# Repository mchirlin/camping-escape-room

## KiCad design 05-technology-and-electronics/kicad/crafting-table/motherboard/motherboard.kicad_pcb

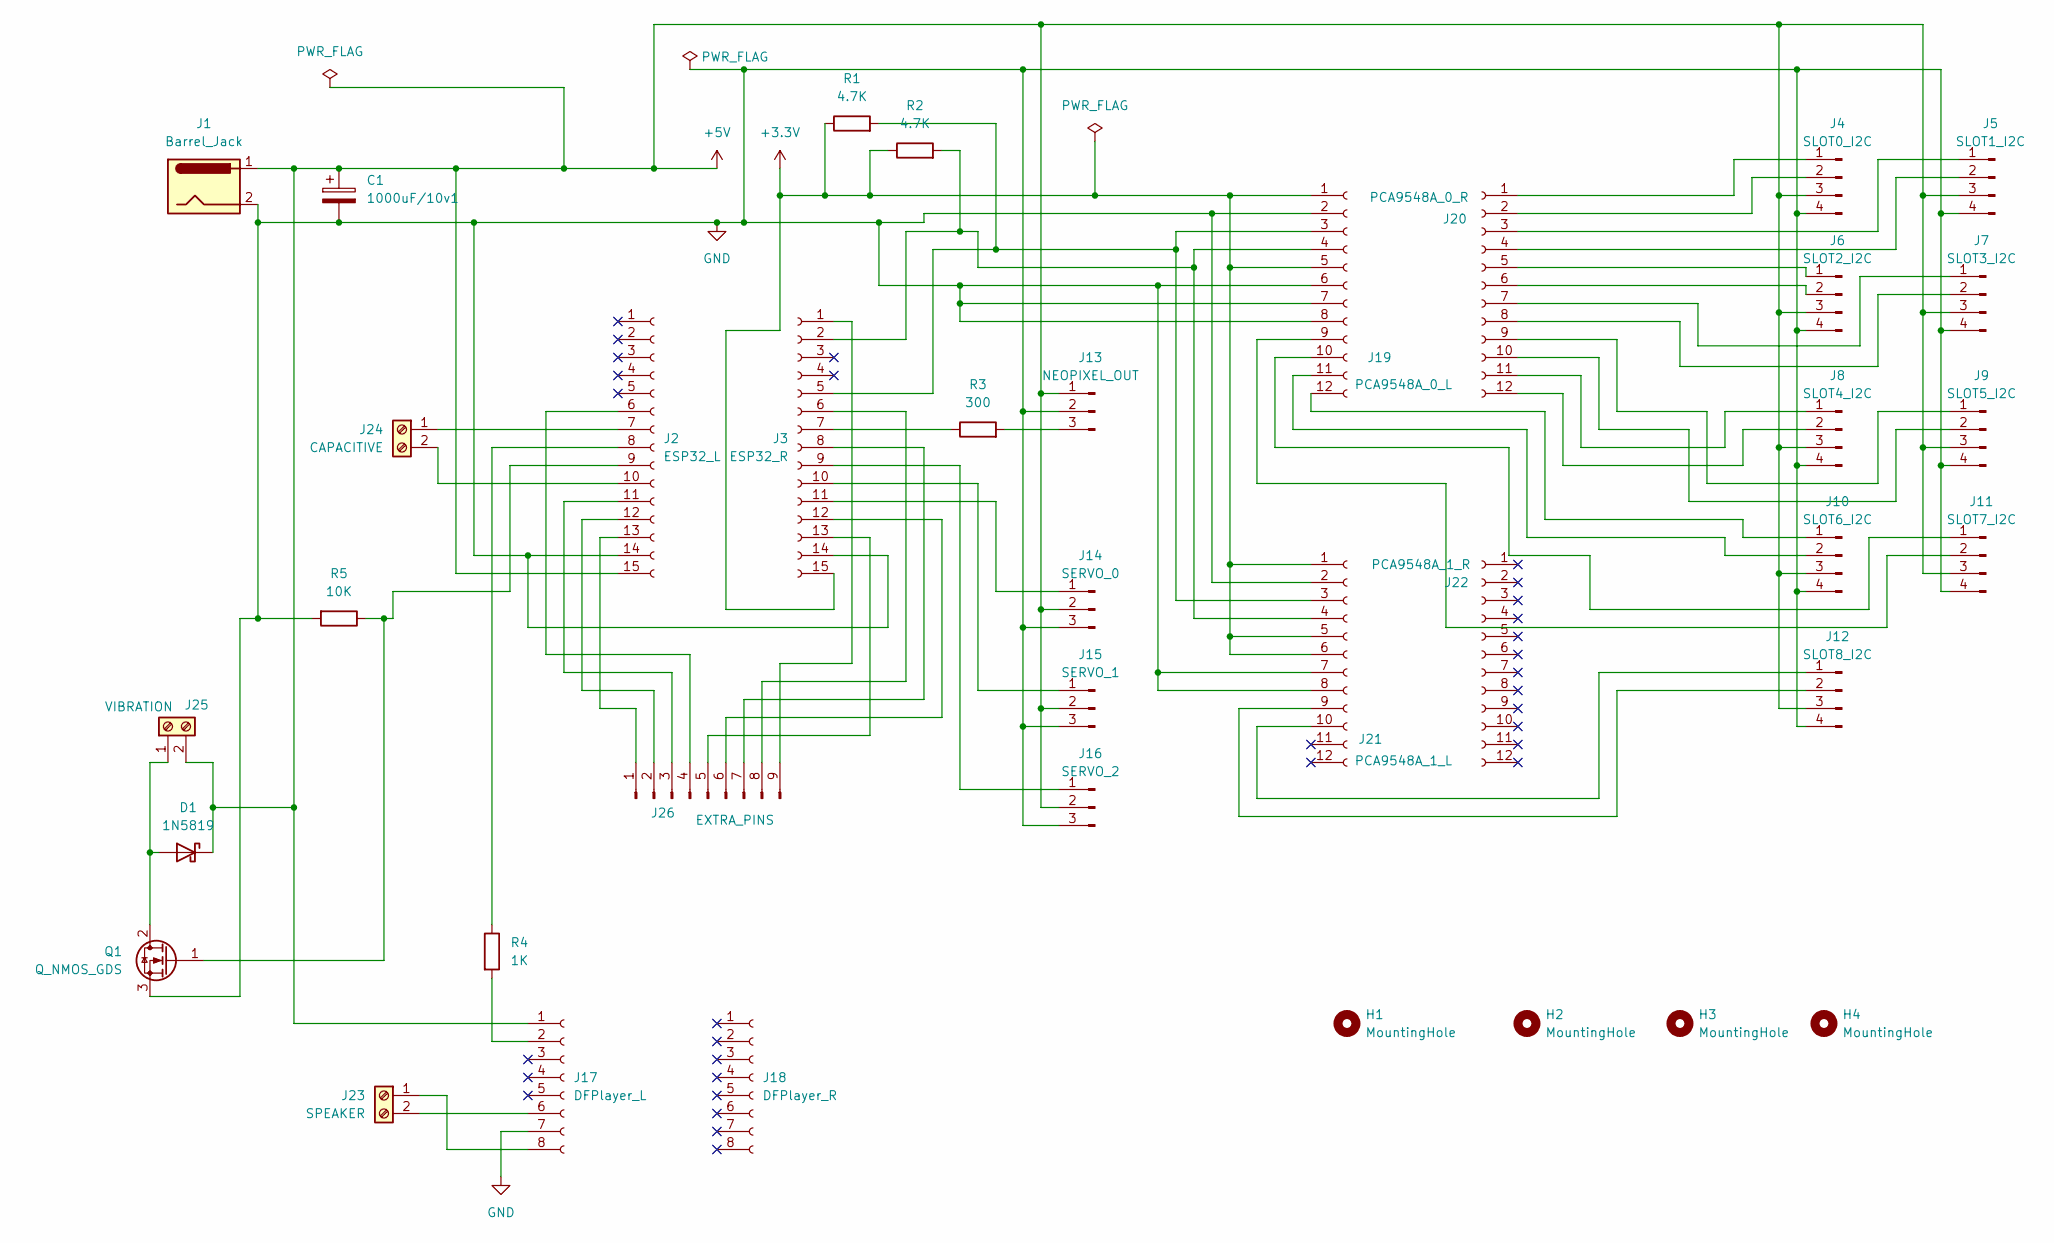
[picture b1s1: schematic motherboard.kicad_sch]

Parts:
C1: 1000uF/10v1; CP_Radial_D10.0mm_P5.00mm
D1: 1N5819; D_DO-41_SOD81_P10.16mm_Horizontal
H1, H2, H3, H4: MountingHole; MountingHole_3.2mm_M3
J1: Barrel_Jack; BarrelJack_Horizontal
J2: ESP32_L; PinSocket_1x15_P2.54mm_Vertical
J3: ESP32_R; PinSocket_1x15_P2.54mm_Vertical
J4: SLOT0_I2C; JST_XH_B4B-XH-A_1x04_P2.50mm_Vertical
J5: SLOT1_I2C; JST_XH_B4B-XH-A_1x04_P2.50mm_Vertical
J6: SLOT2_I2C; JST_XH_B4B-XH-A_1x04_P2.50mm_Vertical
J7: SLOT3_I2C; JST_XH_B4B-XH-A_1x04_P2.50mm_Vertical
J8: SLOT4_I2C; JST_XH_B4B-XH-A_1x04_P2.50mm_Vertical
J9: SLOT5_I2C; JST_XH_B4B-XH-A_1x04_P2.50mm_Vertical
J10: SLOT6_I2C; JST_XH_B4B-XH-A_1x04_P2.50mm_Vertical
J11: SLOT7_I2C; JST_XH_B4B-XH-A_1x04_P2.50mm_Vertical
J12: SLOT8_I2C; JST_XH_B4B-XH-A_1x04_P2.50mm_Vertical
J13: NEOPIXEL_OUT; JST_XH_B3B-XH-A_1x03_P2.50mm_Vertical
J14: SERVO_0; JST_XH_B3B-XH-A_1x03_P2.50mm_Vertical
J15: SERVO_1; JST_XH_B3B-XH-A_1x03_P2.50mm_Vertical
J16: SERVO_2; JST_XH_B3B-XH-A_1x03_P2.50mm_Vertical
J17: DFPlayer_L; PinSocket_1x08_P2.54mm_Vertical
J18: DFPlayer_R; PinSocket_1x08_P2.54mm_Vertical
J19: PCA9548A_0_L; PinSocket_1x12_P2.54mm_Vertical
J20: PCA9548A_0_R; PinSocket_1x12_P2.54mm_Vertical
J21: PCA9548A_1_L; PinSocket_1x12_P2.54mm_Vertical
J22: PCA9548A_1_R; PinSocket_1x12_P2.54mm_Vertical
J23: SPEAKER; TerminalBlock_TE_282834-2_1x02_P2.54mm_Horizontal
J24: CAPACITIVE; TerminalBlock_TE_282834-2_1x02_P2.54mm_Horizontal
J25: VIBRATION; TerminalBlock_TE_282834-2_1x02_P2.54mm_Horizontal
J26: EXTRA_PINS; PinHeader_1x09_P2.54mm_Vertical
Q1: Q_NMOS_GDS; TO-220-3_Vertical
R1, R2: 4.7K; R_Axial_DIN0207_L6.3mm_D2.5mm_P10.16mm_Horizontal
R3: 300; R_Axial_DIN0207_L6.3mm_D2.5mm_P10.16mm_Horizontal
R4: 1K; R_Axial_DIN0207_L6.3mm_D2.5mm_P10.16mm_Horizontal
R5: 10K; R_Axial_DIN0207_L6.3mm_D2.5mm_P10.16mm_Horizontal

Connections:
+3.3V: J3.15, J19.1, J19.5, J21.1, J21.5, J21.6, R1.1, R2.1
+5V: C1.1, D1.1 (K), J1.1, J2.15, J4.3, J5.3, J6.3, J7.3, J8.3, J9.3, J10.3, J11.3, J12.3, J13.1, J14.2, J15.2, J16.2, J17.1, J25.2
GND: C1.2, J1.2, J2.14, J3.14, J4.4, J5.4, J6.4, J7.4, J8.4, J9.4, J10.4, J11.4, J12.4, J13.2, J14.3, J15.3, J16.3, J17.7, J19.2, J19.6, J19.7, J19.8, J21.2, J21.7, J21.8, Q1.3 (S), R5.2
unnamed: D1.2 (A), J25.1, Q1.2 (D)
unnamed: J2.6, J26.4
unnamed: J2.7, J24.1
unnamed: J2.8, R4.1
unnamed: J2.9, Q1.1 (G), R5.1
unnamed: J2.10, J24.2
unnamed: J2.11, J26.3
unnamed: J2.12, J26.2
unnamed: J2.13, J26.1
unnamed: J3.7, R3.1
unnamed: J10.1, J19.12
unnamed: J10.2, J19.11
unnamed: J11.1, J19.10
unnamed: J11.2, J19.9
unnamed: J12.1, J21.10
unnamed: J12.2, J21.9
unnamed: J13.3, R3.2
unnamed: J3.11, J14.1
unnamed: J3.10, J15.1
unnamed: J3.9, J16.1
unnamed: J17.2, R4.2
unnamed: J17.6, J23.2
unnamed: J17.8, J23.1
unnamed: J3.5, J19.3, J21.3, R1.2
unnamed: J3.2, J19.4, J21.4, R2.2
unnamed: J4.1, J20.1
unnamed: J4.2, J20.2
unnamed: J5.1, J20.3
unnamed: J5.2, J20.4
unnamed: J6.1, J20.5
unnamed: J6.2, J20.6
unnamed: J7.1, J20.7
unnamed: J7.2, J20.8
unnamed: J9.1, J20.9
unnamed: J9.2, J20.10
unnamed: J8.1, J20.11
unnamed: J8.2, J20.12
unnamed: J3.13, J26.5
unnamed: J3.12, J26.6
unnamed: J3.8, J26.7
unnamed: J3.6, J26.8
unnamed: J3.1, J26.9

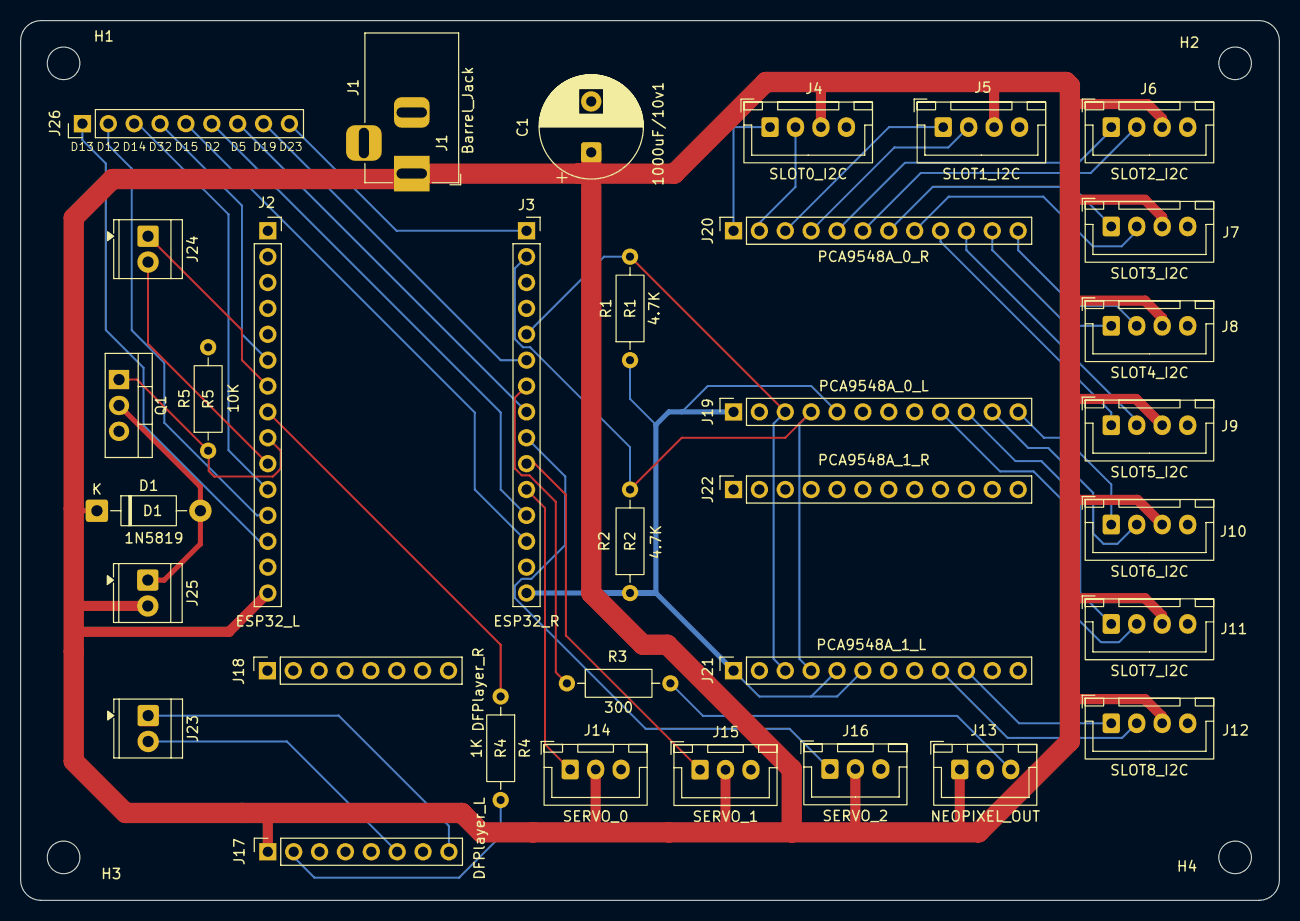
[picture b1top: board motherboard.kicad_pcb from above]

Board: 2 copper layers, 123.6 x 86.4 mm, 38 parts (0 on the bottom side), 45 nets.

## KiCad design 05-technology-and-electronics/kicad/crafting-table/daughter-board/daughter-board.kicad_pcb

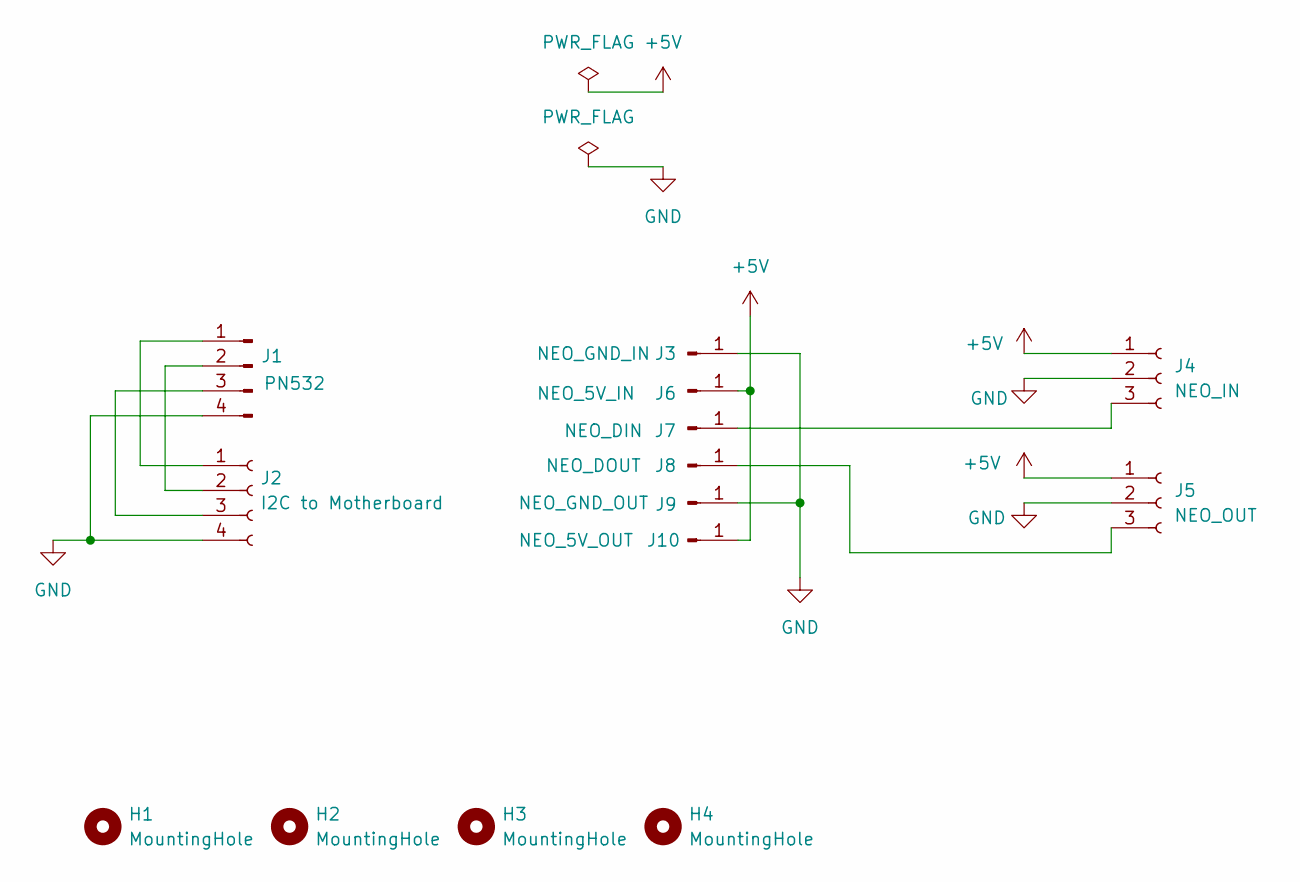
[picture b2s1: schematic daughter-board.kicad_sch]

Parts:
H1, H2, H3, H4: MountingHole; MountingHole_3.2mm_M3
J1: PN532; PinHeader_1x04_P2.54mm_Vertical
J2: I2C to Motherboard; JST_XH_B4B-XH-A_1x04_P2.50mm_Vertical
J3: NEO_GND_IN; PinHeader_1x01_P2.54mm_Vertical
J4: NEO_IN; JST_XH_B3B-XH-A_1x03_P2.50mm_Vertical
J5: NEO_OUT; JST_XH_B3B-XH-A_1x03_P2.50mm_Vertical
J6: NEO_5V_IN; PinHeader_1x01_P2.54mm_Vertical
J7: NEO_DIN; PinHeader_1x01_P2.54mm_Vertical
J8: NEO_DOUT; PinHeader_1x01_P2.54mm_Vertical
J9: NEO_GND_OUT; PinHeader_1x01_P2.54mm_Vertical
J10: NEO_5V_OUT; PinHeader_1x01_P2.54mm_Vertical

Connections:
+5V: J4.1, J5.1, J6.1 (Pin_1_1), J10.1 (Pin_1_1)
GND: J1.4, J2.4, J3.1 (Pin_1_1), J4.2, J5.2, J9.1 (Pin_1_1)
unnamed: J1.1, J2.1
unnamed: J1.2, J2.2
unnamed: J1.3, J2.3
unnamed: J4.3, J7.1 (Pin_1_1)
unnamed: J5.3, J8.1 (Pin_1_1)

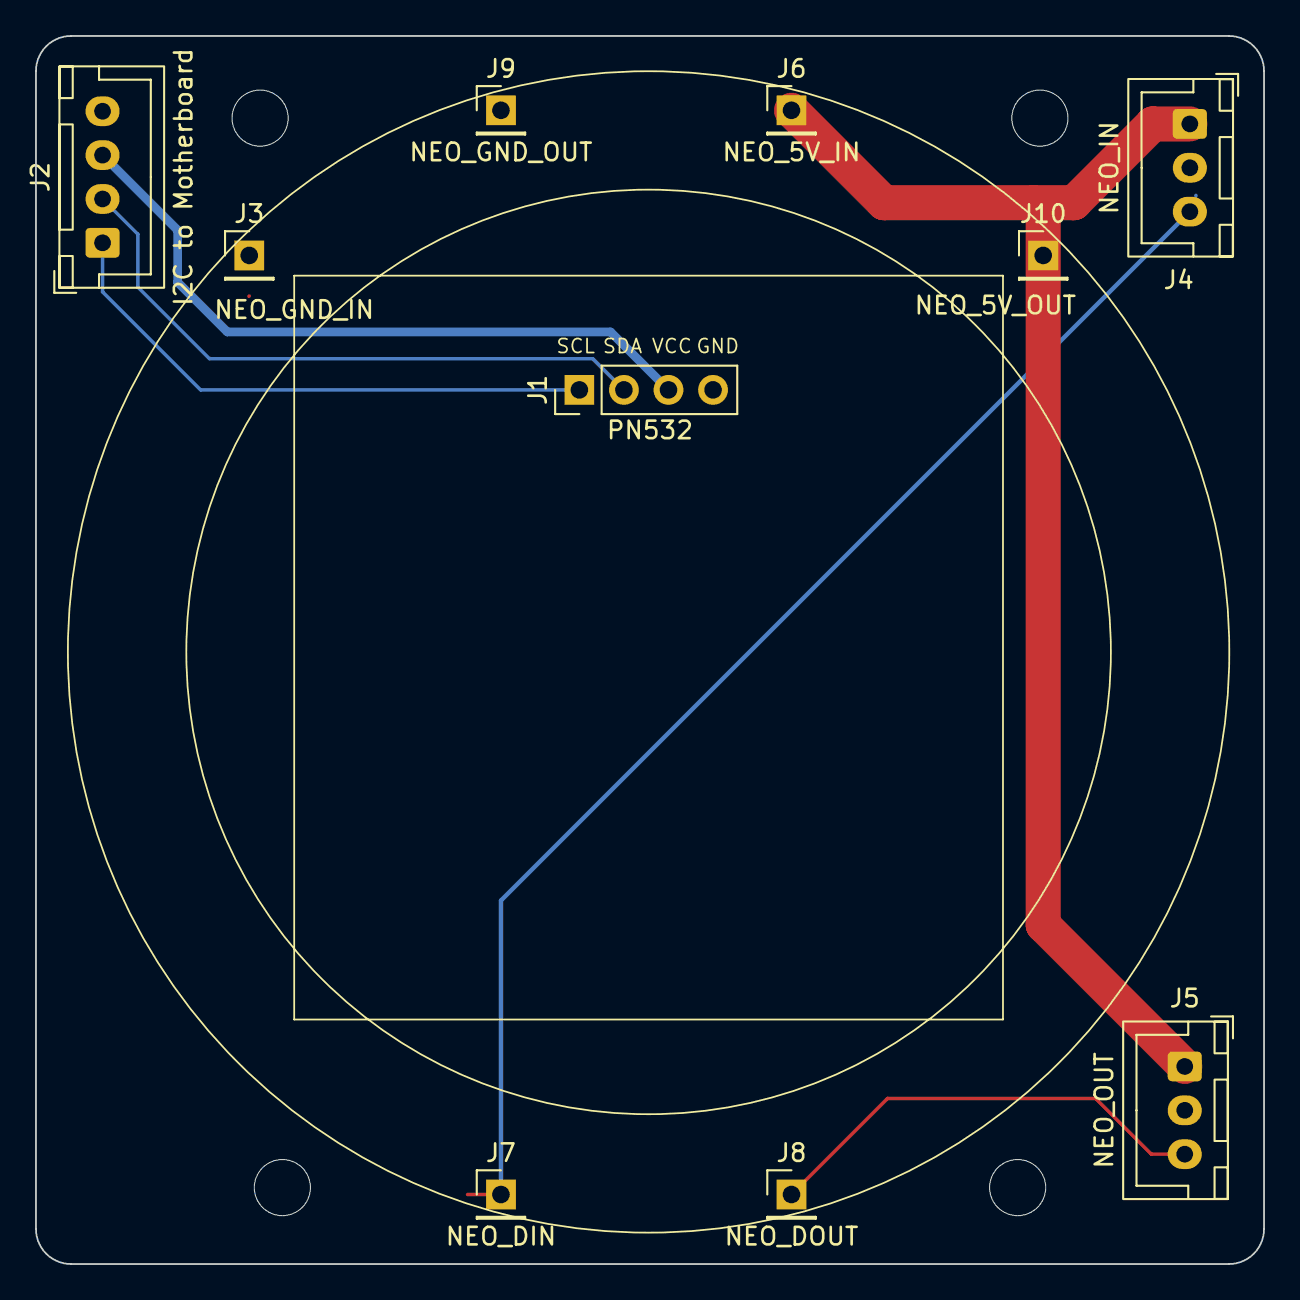
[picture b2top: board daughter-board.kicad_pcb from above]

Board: 2 copper layers, 70.0 x 70.0 mm, 14 parts (0 on the bottom side), 7 nets.

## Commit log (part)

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2026-04-26 Initial commit: Minecraft camping escape room project with fog-of-war map
2026-04-26 Fix: simplify vite config for CI build, remove dev-only plugins
2026-04-26 Fix: match base path to actual repo name camping-escape-room
2026-04-26 Fix CI: use npm ci + npm run build, remove tsc from build script
2026-04-26 Fix CI: move sharp to optional deps, skip in CI build
2026-04-26 Fix CI: remove --no-optional flag, let rollup install platform binaries
2026-04-26 Fix CI: use Node 22, clean install, remove lockfile from git
2026-04-26 Fix: use BASE_URL for all asset paths, copy marker textures to public
2026-04-26 Add local marker API server + marker-db abstraction layer
2026-04-26 Paper background, opaque fog, map border, compass heading, fullscreen button, marker collect
2026-04-26 Map border: use actual map_background.png torn paper texture, black outside
2026-04-26 Fix: paper background, no fog drawing, torn border frame with black outside
2026-04-26 Fix rendering order: black bg → paper texture → terrain on top
2026-04-26 Widen map border to 3px
2026-04-26 Map levels 0-2 with Minecraft sizes, max zoom, Alex face, terrain gen API restored
2026-04-26 Fix map levels: 0-2 with area scaling, fix broken renderer, add zoom limits, Alex face, terrain gen API
2026-04-26 Map rotation, WASD heading, quadrant discovery, forest/park terrain, reveal all
    - Fix map background rotating with terrain tiles
    - WASD movement now relative to heading direction
    - Map quadrants appear as player discovers them
    - Add forest from OSM multipolygon relations (join open ring segments)
    - Add park terrain for campsites (lighter green clearings)
    - Add sports fields as sand terrain
2026-04-26 Add multi-region support with 2632 Depaul Dr location
    - Generate terrain data for Depaul Dr area
    - Split terrain into per-region files (terrain-lakefairfax.json, terrain-depaul.json)
    - Add regions.json index for available map regions
    - Add region selector dropdown in simulation UI
    - Region selection via ?region=<id> URL parameter
    - Switching regions reloads with the new region param
2026-04-26 Persist selected region in localStorage across page loads
2026-04-26 Fix markers not rotating with map and GPS not following player
    - Apply rotation transform to marker rendering so items rotate with the map
    - Auto-center map on player position in GPS mode
2026-04-26 Make Reveal All button always visible (not just simulation mode)
2026-04-26 Fix fullscreen button on mobile, revert reveal all visibility
2026-04-26 Reset heading to 0 (north up) when leaving orientation mode
2026-04-26 Add pixel art favicon and apple-touch-icon for iOS home screen
2026-04-26 Simplify icon: remove border, crossroads, and compass needle
2026-04-26 Add Remove All Items button to clear all placed markers
2026-04-26 Reset discovered quadrants when resetting fog
2026-04-26 Fix reset fog: use empty sets instead of clearing map (null = show all)
2026-04-26 Add confirmation dialog to Reveal All button
2026-04-26 Fix extra pixels: make terrain grids square at all zoom levels
2026-04-26 Update escape room plan: integrate fog map + compass into game flow
    - Maps (1-2 devices) unlocked by crafting Map recipe #4
    - MCompass points to tent/crafting table (home base), not dig site
    - Updated TODO with completed fog map tasks
    - Updated game day setup, reset, and pack checklist
2026-04-26 Remove hand-drawn treasure map — dig site is now a marker on the fog map
2026-04-26 Remove cake bonus recipe and its ingredients (wheat, milk, sugar, egg)
2026-04-26 Update map markers to match escape room blocks and locations
    Blocks: Wood Plank, Stick, Iron Ingot, String, Gold Ingot, Paper, Compass, Diamond
    Locations: Creeper, Crafting Table, Mine, Dig Site
    Removed: chest, emerald, redstone, tnt, spawn, danger, star
2026-04-26 Redo stick (diagonal Minecraft style) and compass (red/white needle on grey disc) icons
2026-04-26 Replace marker icons with real Minecraft textures from textures folder
    - stick, paper, string, compass, diamond, iron, gold, wood planks from item/block textures
    - Creeper face extracted from entity skin sheet
    - Mine icon uses iron pickaxe texture
    - Crafting table uses front face texture
2026-04-26 Fix creeper icon (clean pixel art face) and use diamond pickaxe for dig site
2026-04-27 Only auto-center on player in orientation mode, allow free panning in north-up mode
2026-04-27 Add crafting table materials list to TODO
2026-04-27 Add servo door section to TODO: 3 doors, servos, driver, mounts, firmware
2026-04-27 Update servo doors: gravity latch design with reed switch auto-close
2026-04-27 Detail servo door design: hidden servos, slot latch, flush doors, full build steps
2026-04-27 Update TODO and SHOPPING-LIST with all materials: table lumber, servo doors, TNT chest, new block counts
2026-04-27 Add prioritized build timeline targeting mid-July
2026-04-27 Add plywood wooden props to ordering and timeline (sword, pickaxe, shovel, rod)
2026-04-27 Remove PCA9685 — drive 3 servos directly from ESP32 GPIO pins
2026-04-28 Redesign doors: servo push-open + ball catch, piano hinges, remove reed switches
2026-04-28 Rewrite timeline: individual checkboxes, updated door design, detailed packing list
2026-04-28 Add 3 wood stains to shopping list (light, medium, dark for crafting table)
2026-04-28 Replace light/medium stains with danish oil + watered-down acrylics, keep espresso
2026-04-28 Fix Appian HQ coordinates, fix fog showing revealed on first load (init empty quadrant sets)
2026-04-28 Fix fallback terrain filename (terrain-data.json no longer exists)
2026-04-28 Fix terrain-utils: use Math.ceil for grid coverage, keep square grid
2026-04-28 fix: move MAP_LEVEL_CONFIG declaration before first usage
    Resolves ReferenceError caused by temporal dead zone — the const was
    declared after the loop that referenced it.
2026-04-28 fix: update test assertions and show sim hints on toggle
    - Adjust fog-engine property test to use strict radius boundary check
    - Update map-interaction zoom clamp expectations to match new limits
    - Show/hide simHints element alongside simBanner in UI overlay
2026-04-28 Fix all 7 failing tests: zoom clamps, UI overlay hints/compass, fog engine boundary tolerance
    - Update zoom clamp tests to match actual MIN_ZOOM=-3, MAX_ZOOM=6
    - Restore createSimulationHints() call in init
    - Toggle simHints visibility in setSimulationVisible
    - Set initial compass arrow transform to rotate(0deg)
    - Fix fog engine property test: add 1m tolerance and bbox bounds check for square grid edge tiles
2026-04-30 fog map: auto-select closest region via GPS, add simulation exit button
2026-04-30 remove WASD sim controls, fix mobile UI with flexbox corner groups
2026-05-01 add purple simulation favicons for distinct iPhone home screen icon
2026-05-02 Add recipe cards and block icons for crafting puzzles
2026-05-02 Add explorer's diary narrative and generator
2026-05-02 Update stencils, add generator script and 3D block model
2026-05-02 Add PCB designs, Arduino sketches, and electronics documentation
2026-05-02 Update fog map: marker icons, crafting link, and main logic
2026-05-02 Add Minecraft sound effects for escape room puzzles
2026-05-02 Update TODO and timeline
2026-05-02 Add __pycache__ and .history to gitignore
